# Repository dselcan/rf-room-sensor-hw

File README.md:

# rf-room-sensor-hw

## Short summary

The RF Room Sensor device is a remote monitoring device, capable of measuring the local temperature and hummidity at the location where it is placed. It is designed to be powered by 3 AAA rechargable cells, with an expected charge lifetime of 5 years. The data is sent over the 433 MHz ISM band as a Manchester-modulated OOK signal and collected by a central node, featuring a 433 MHz receiver. The data is then stored in a database and exposed to the user over a local website. 

## Detailed design description and tradeoffs

The primary design constraints are a 5 year lifetime and a form factor comptabile with the Hammond Manufacturing 1551V3WH enclosure - thus, the final size of the device is 60 mm x 60 mm x 20 mm. The sensor used is the TI HDC1080, offering a ±0.2°C temperature measurement accuracy and a ±2% relative hummiditiy measurement accuracy. The device is controlled by an ATtiny404 microcontroller, which features a sufficient low power mode to achieve the expected 5 year charge lifetime. The RF data transmission interval is approximately 20 seconds, where an external 433 MHz transmitter is used as the transmitting module - when not in use, it is powered off by using a P-type MOSFET. The battery holder is constructed using naked battery tabs and the PCB, which is then screwed into the enclosure - no additional battery holders are envisioned, due to form factor limitations of the enclosure.

Additionally, a air quality monitor is envisioned to also be supported - however, at the time when the project was designed, no sufficiently low power air quaility monitors existed and as such, it was never populated. The air quality part of the circuit (right side of the schematic) is as such not tested and not included in the BOM.

## Assembly instructions

Manufacture the PCBs according to the provided project. The BOM is present in the associated BOM.csv file.
Solder all the components to the PCB - ignore the remaining components on the PCB that are required for the air quality monitor.
Before solderign the 433 MHz transmitter, do a fit check to the enclosure - if required, the header on the 433 MHz transmitter can be desoldered to gain the extra space.
Solder the 433 MHz transmitter to the RF header using approximately 5 cm long thin wires - Pad 0 is GND, Pad 1 is the data pin and Pad 2 is the VCC supply pin. Wrap the transmitter in a non-conductive tape to prevent short circuits with the battery pads.
Carefully place the batteries into the holders - beware the polarity, no reverse polarity protection is present.
Immediately screw the PCB into the bottom half of the enclosure - this will fix the batteries into place.

## License

The whole RF Room Sensor project is licensed under a BSD license.

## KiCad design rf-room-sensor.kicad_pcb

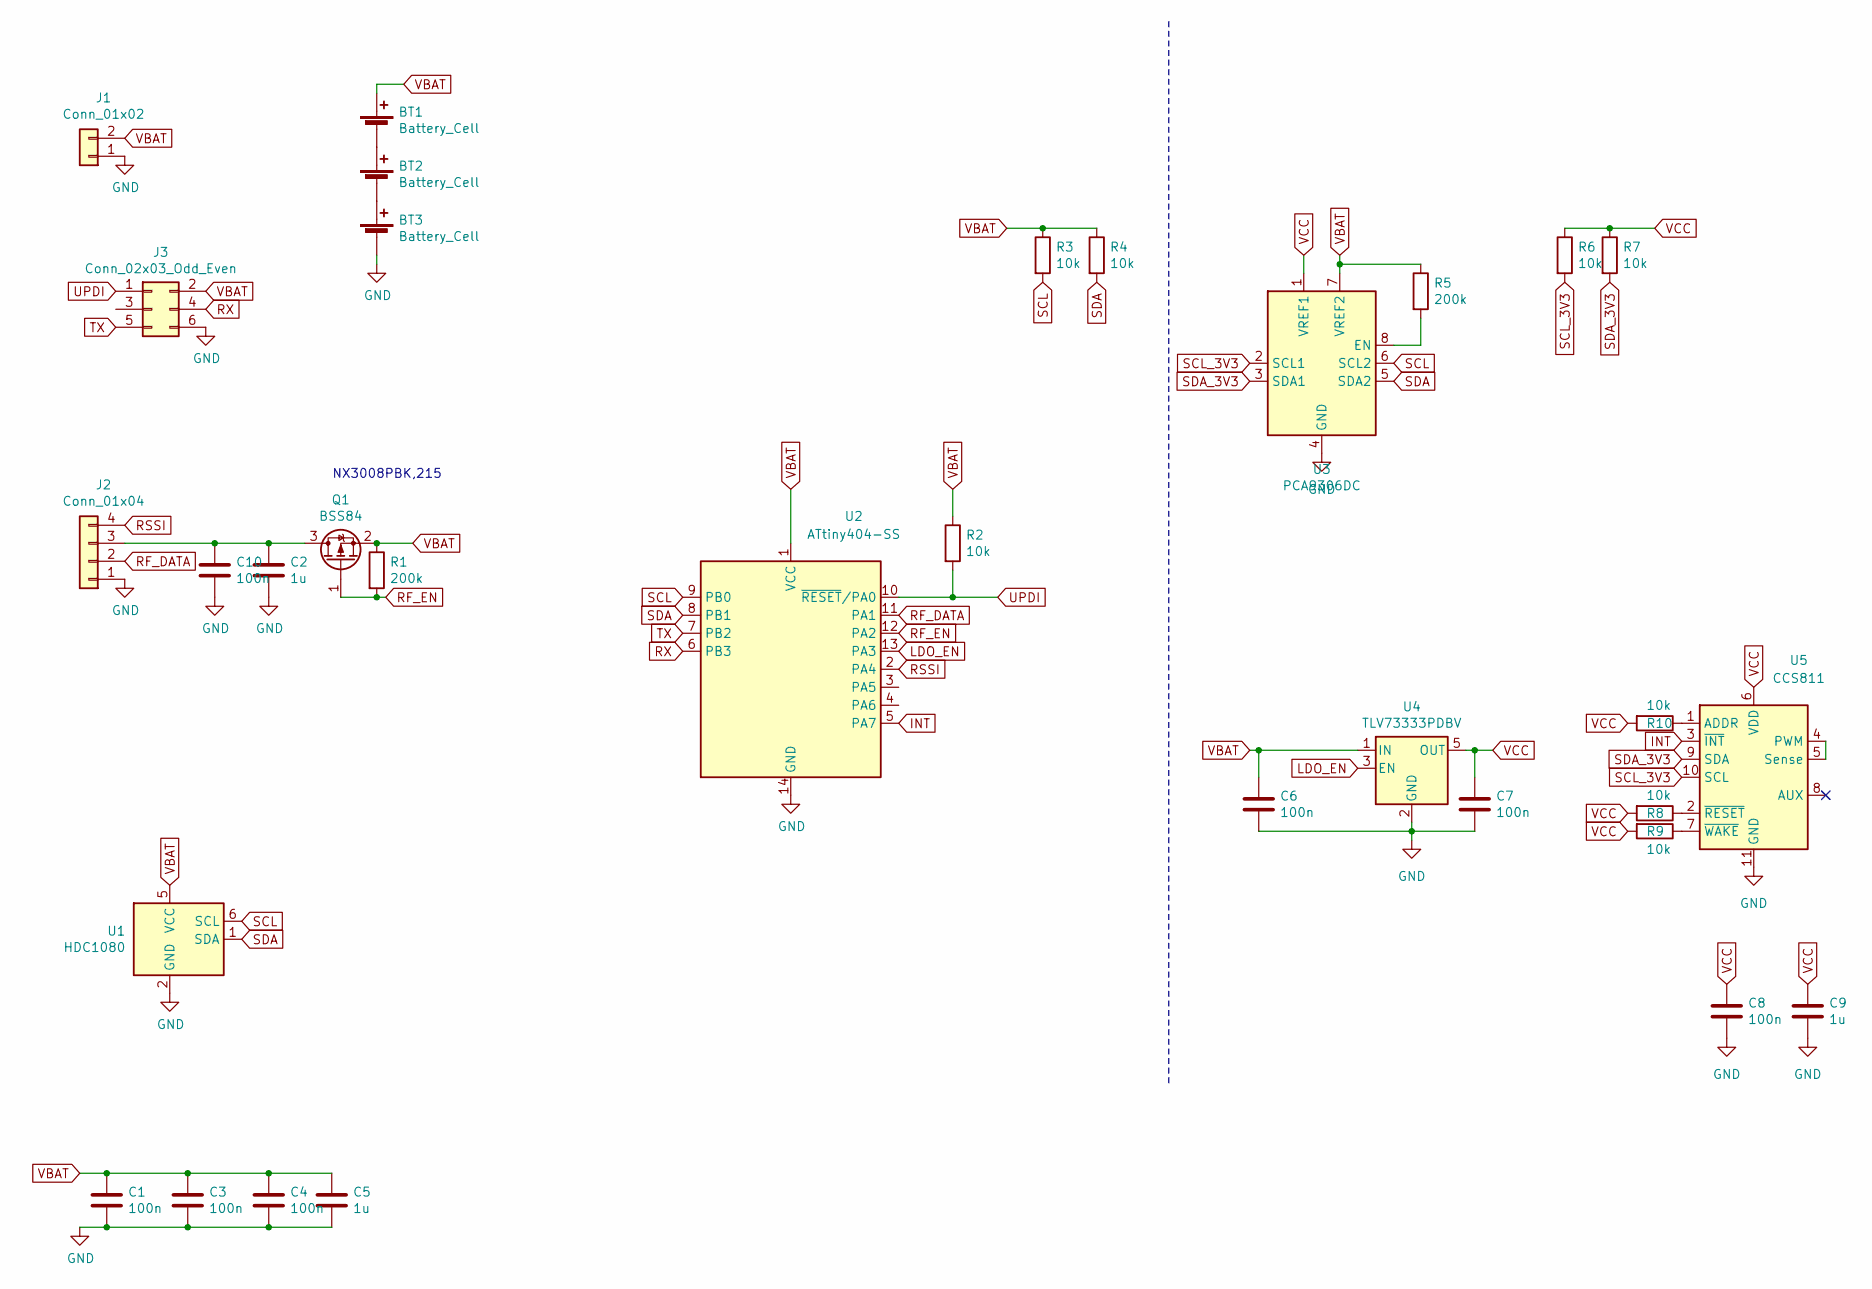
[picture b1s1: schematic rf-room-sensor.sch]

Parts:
BT1, BT2, BT3: Battery_Cell; BatteryHolder_Keystone_56_AAA
C1, C3, C4, C6, C7, C8, C10: 100n; C_0603_1608Metric_Pad1.08x0.95mm_HandSolder
C2, C5, C9: 1u; C_0603_1608Metric_Pad1.08x0.95mm_HandSolder
J1: Conn_01x02; PinHeader_1x02_P2.54mm_Vertical
J2: Conn_01x04; PinHeader_1x04_P2.54mm_Vertical
J3: Conn_02x03_Odd_Even; PinHeader_2x03_P2.54mm_Vertical
Q1: BSS84; SOT-23
R1, R5: 200k; R_0603_1608Metric_Pad0.98x0.95mm_HandSolder
R2, R3, R4, R6, R7, R8, R9, R10: 10k; R_0603_1608Metric_Pad0.98x0.95mm_HandSolder
U1: HDC1080; Texas_PWSON-N6
U2: ATtiny404-SS; SOIC-14_3.9x8.7mm_P1.27mm
U3: PCA9306DC; VSSOP-8_2.3x2mm_P0.5mm
U4: TLV73333PDBV; SOT-23-5
U5: CCS811; AMS_LGA-10-1EP_2.7x4mm_P0.6mm

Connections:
GND: BT3.2 (-), C1.2, C2.2, C3.2, C4.2, C5.2, C6.2, C7.2, C8.2, C9.2, C10.2, J1.1, J2.1, J3.6, U1.2 (GND), U2.14 (GND), U3.4 (GND), U4.2 (GND), U5.11 (GND)
INT: U2.5 (PA7), U5.3 (~INT)
LDO_EN: U2.13 (PA3), U4.3 (EN)
unnamed: BT1.2 (-), BT2.1 (+)
unnamed: BT2.2 (-), BT3.1 (+)
unnamed: C2.1, C10.1, J2.3, Q1.3 (D)
unnamed: R5.2, U3.8 (EN)
unnamed: R8.1, U5.2 (~RESET)
unnamed: R9.1, U5.7 (~WAKE)
unnamed: R10.1, U5.1 (ADDR)
unnamed: U5.4 (PWM), U5.5 (Sense)
RF_DATA: J2.2, U2.11 (PA1)
RF_EN: Q1.1 (G), R1.2, U2.12 (PA2)
RSSI: J2.4, U2.2 (PA4)
RX: J3.4, U2.6 (PB3)
SCL: R3.2, U1.6 (SCL), U2.9 (PB0), U3.6 (SCL2)
SCL_3V3: R6.2, U3.2 (SCL1), U5.10 (SCL)
SDA: R4.2, U1.1 (SDA), U2.8 (PB1), U3.5 (SDA2)
SDA_3V3: R7.2, U3.3 (SDA1), U5.9 (SDA)
TX: J3.5, U2.7 (PB2)
UPDI: J3.1, R2.2, U2.10 (~RESET~/PA0)
VBAT: BT1.1 (+), C1.1, C3.1, C4.1, C5.1, C6.1, J1.2, J3.2, Q1.2 (S), R1.1, R2.1, R3.1, R4.1, R5.1, U1.5 (VCC), U2.1 (VCC), U3.7 (VREF2), U4.1 (IN)
VCC: C7.1, C8.1, C9.1, R6.1, R7.1, R8.2, R9.2, R10.2, U3.1 (VREF1), U4.5 (OUT), U5.6 (VDD)

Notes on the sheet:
NX3008PBK,215

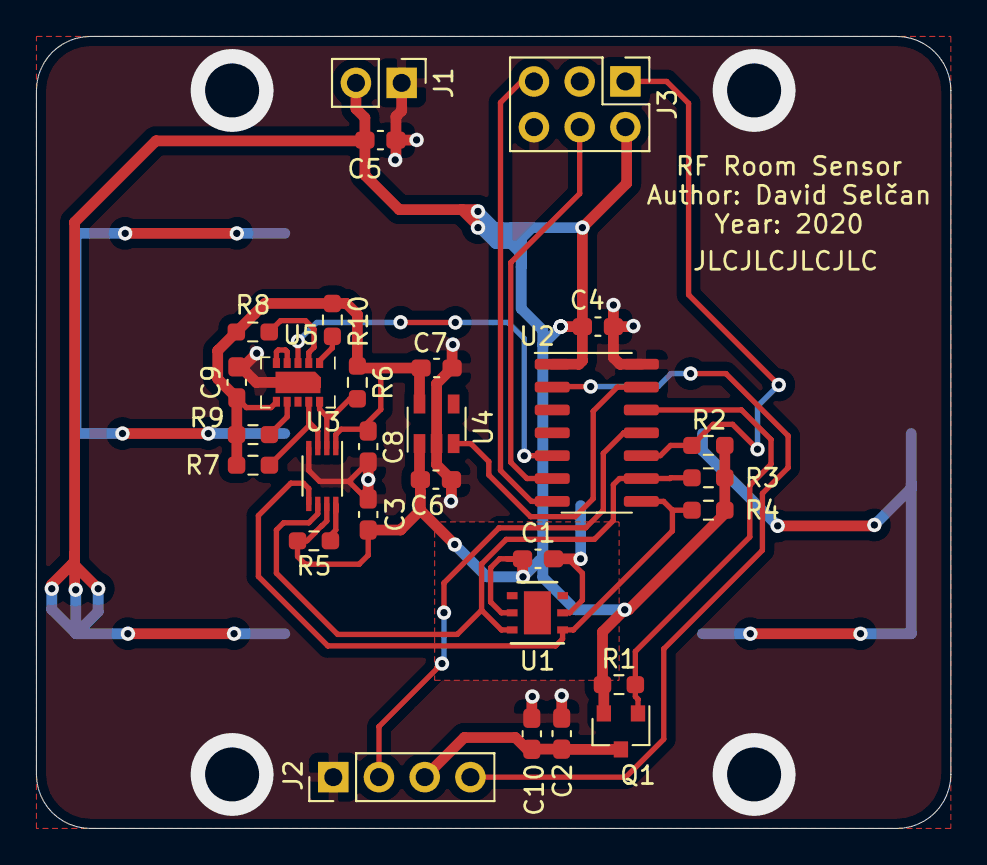
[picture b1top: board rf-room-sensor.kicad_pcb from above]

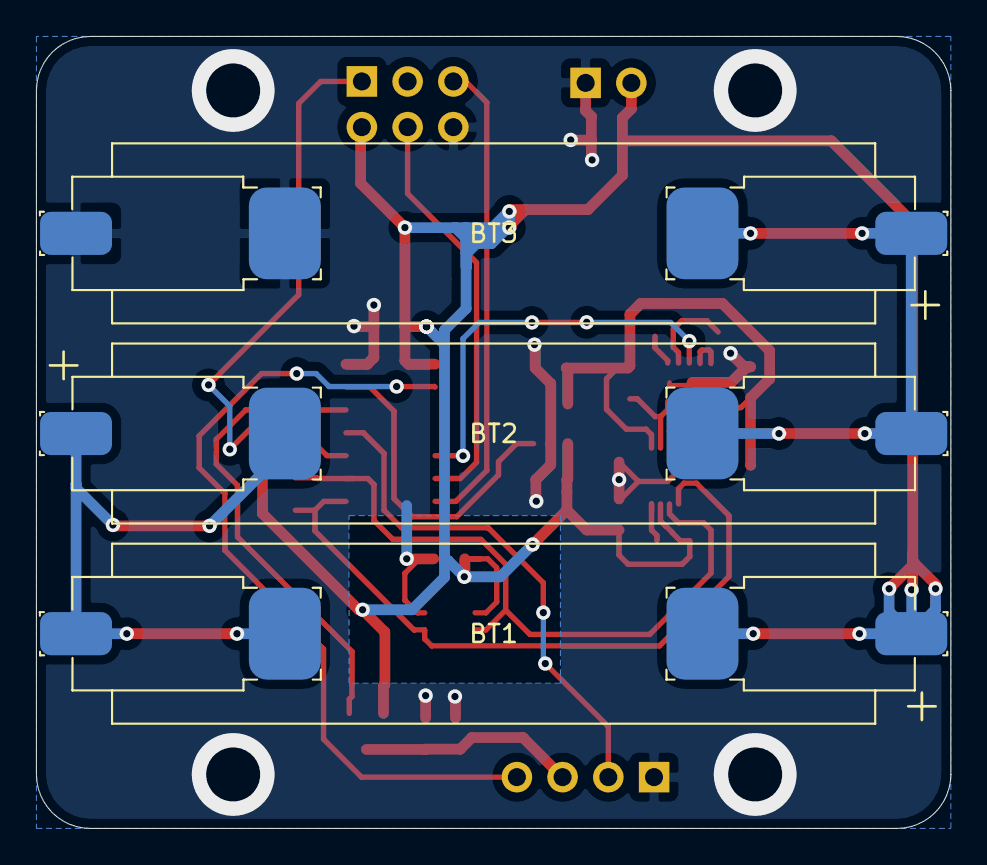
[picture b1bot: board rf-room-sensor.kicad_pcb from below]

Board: 2 copper layers, 50.8 x 44.0 mm, 32 parts (3 on the bottom side), 23 nets.

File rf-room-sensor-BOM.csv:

Id,Designator,Package,Quantity,Designation,Supplier and ref
1,"BT1,BT3,BT2",BatteryHolder_Keystone_56_AAA,6,Battery_Cell,
2,"R10,R9,R8,R4,R3,R2",R_0603_1608Metric_Pad0.98x0.95mm_HandSolder,6,10k,https://eu.mouser.com/ProductDetail/652-CR0603FX-1002ELF
3,Q1,SOT-23,1,"NX3008PBK,215 ",https://eu.mouser.com/ProductDetail/771-NX3008PBK%2c215
4,U2,SOIC-14_3.9x8.7mm_P1.27mm,1,ATtiny404-SS,https://eu.mouser.com/ProductDetail/579-ATTINY404-SSN
5,U1,Texas_PWSON-N6,1,HDC1080,https://eu.mouser.com/ProductDetail/595-HDC1080DMBR
6,"C5,C2",C_0603_1608Metric_Pad1.08x0.95mm_HandSolder,2,1u,https://eu.mouser.com/ProductDetail/187-CL10A105KA8NNNC
7,"C10,C4,C3,C1",C_0603_1608Metric_Pad1.08x0.95mm_HandSolder,4,100n,https://eu.mouser.com/ProductDetail/963-TMK107BJ104MA-T
,,,,,
,Non-PCB items,,,,
,N/A,Enclosure 1551V3WH ,1,,https://eu.mouser.com/ProductDetail/546-1551V3WH
,N/A,"Screw 3,0 x 15 self-tapping",4,,

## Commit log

2021-10-20 Initial commit
    Initial commit
2021-10-20 Added README, updated BOM
    Added README, updated BOM
